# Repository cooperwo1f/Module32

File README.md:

# Base Repository for Module32
Contains PCB hardware source and output files, as well as STM32CubeIDE project file/Makefile (for both IDE and CLI based workflows).
Also contains basic user setup to allow natural printf usage (through SWO) using ITM port 0, as well as comment-free user source file.
Recommendation is to use STM32CubeIDE for GUI configuration as well as initial debugging, then move to vim/emacs for bulk of development.

## Module32 PINOUT

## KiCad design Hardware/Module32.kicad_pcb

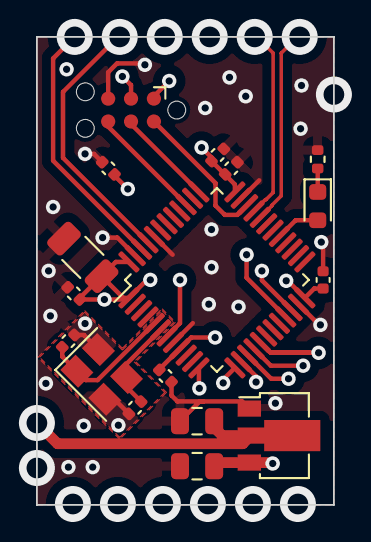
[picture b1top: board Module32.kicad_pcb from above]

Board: 4 copper layers, 16.5 x 26.0 mm, 17 parts (0 on the bottom side), 11 nets.

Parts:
C1, C2, C3, C4, C5, C9: 100nF; C_0402_1005Metric
C6: 4.7uF; C_1206_3216Metric
C7, C8: 10uF; C_0805_2012Metric
C10, C11: 10pF; C_0402_1005Metric
D1: LED_GREEN; LED_0603_1608Metric
J2: Conn_ARM_SWD_TagConnect_TC2030-NL; Tag-Connect_TC2030-IDC-NL_2x03_P1.27mm_Vertical
R1: 5.1k; R_0402_1005Metric
U1: HT7533-1-SOT89; SOT-89-3
U2: STM32F103C8Tx; LQFP-48_7x7mm_P0.5mm
Y1: Crystal_GND24; Crystal_SMD_3225-4Pin_3.2x2.5mm

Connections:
/LED: D1.2 (A), U2.29 (PA8)
/OSC_IN: C10.1, U2.5 (PD0), Y1.1
/OSC_OUT: C11.1, U2.6 (PD1), Y1.3
/SWCLK: J2.4 (SWCLK), U2.37 (PA14)
/SWDIO: J2.2 (SWDIO), U2.34 (PA13)
/SWO: J2.6 (SWO), U2.39 (PB3)
/~RST: C9.1, J2.3 (~RESET), U2.7 (NRST)
GND: C1.2, C2.2, C3.2, C4.2, C5.2, C6.2, C7.2, C8.2, C9.2, C10.2, C11.2, J2.5 (GND), R1.2, U1.1 (GND), U2.8 (VSSA), U2.23 (VSS), U2.35 (VSS), U2.44 (BOOT0), U2.47 (VSS), Y1.2, Y1.4
unnamed: D1.1 (K), R1.1
unnamed: C7.1, U1.2 (VIN)
VCC: C1.1, C2.1, C3.1, C4.1, C5.1, C6.1, C8.1, J2.1 (VCC), U1.3 (VOUT), U2.1 (VBAT), U2.9 (VDDA), U2.24 (VDD), U2.36 (VDD), U2.48 (VDD)

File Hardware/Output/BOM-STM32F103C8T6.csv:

Comment,Designator,Footprint,LCSC
Crystal_GND24,Y1,Crystal_SMD_3225-4Pin_3.2x2.5mm,C13738
HT7533-1-SOT89,U1,SOT-89-3,C14289
100nF,"C1,C2,C3,C4,C5,C9",C_0402_1005Metric,C1525
10uF,"C7,C8",C_0805_2012Metric,C15850
5.1k,R1,R_0402_1005Metric,C25905
4.7uF,C6,C_1206_3216Metric,C29823
10pF,"C10,C11",C_0402_1005Metric,C32949
LED_GREEN,D1,LED_0603_1608Metric,C72041
STM32F103C8Tx,U2,LQFP-48_7x7mm_P0.5mm,C8734

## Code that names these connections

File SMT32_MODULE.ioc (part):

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Mcu.Name=STM32F103C(8-B)Tx
Mcu.Package=LQFP48
Mcu.UserName=STM32F103C8Tx
PA13.Mode=Trace_Asynchronous_SW
PA13.Signal=SYS_JTMS-SWDIO
PA14.Mode=Trace_Asynchronous_SW
PA14.Signal=SYS_JTCK-SWCLK
PA8.GPIOParameters=GPIO_Label
PA8.GPIO_Label=LED
PA8.Signal=GPIO_Output
PB3.Mode=Trace_Asynchronous_SW
PB3.Signal=SYS_JTDO-TRACESWO
PD0-OSC_IN.Mode=HSE-External-Oscillator
PD0-OSC_IN.Signal=RCC_OSC_IN
PD1-OSC_OUT.Mode=HSE-External-Oscillator
PD1-OSC_OUT.Signal=RCC_OSC_OUT
RCC.HSEDivPLL=RCC_HSE_PREDIV_DIV2
RCC.HSE_VALUE=16000000
RCC.SYSCLKFreq_VALUE=72000000
RCC.SYSCLKSource=RCC_SYSCLKSOURCE_PLLCLK
board=custom

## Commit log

2023-12-20 Create LICENSE
2023-12-20 removed binary that should be in system path
2023-12-20 Update pinout
2023-12-20 added quiet flag to makefile for better viewing
2023-12-21 fixed spelling issue
2024-04-24 added clangd compile flags generation
2024-04-24 non-change
2024-04-24 fixed formatting
2024-04-24 added compile flag generation
2024-06-20 added basic LED control code
2024-06-20 changed to st-flash and added ITM printf trace
2024-06-20 changed back to LED
2024-06-20 added timer pwm output using cubeIDE
2024-06-20 added timer3 and timer4 in cubeide configurator
2024-06-20 implemented basic software PWM
2024-06-20 changed GPIO ports to fix mismatched blue and green channels
2024-06-20 removed unnecessary references to timer 4
2024-06-20 removed final references, added comments
2024-06-20 removed manual user code configuration
2024-06-20 added cubemx configuration
2024-06-20 fixed errors
2024-06-20 revert to old .ld file
2024-12-18 added hardware files
2024-12-18 added kicad files to ignore
2024-12-18 moved stm32cube config to firmware
2024-12-18 added img, gerber, lib
2024-12-18 fixed naming issues
2024-12-18 universal rename
2024-12-18 changed firmware name
2024-12-18 lib -> Library
